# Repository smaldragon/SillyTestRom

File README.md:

# SillyTestRom

"SillyTestRom" is a simple discrete logic mapper for the famicom/clone that I made for my own personal messing around with homebrew, there are currently no plans to use this in anything.

* 512 KiB PRG-FLASH (partially re-writabble for game saves)
* 8KiB CHR-RAM
* Arbitrary Nametable Mirroring!

I mainly see this as an extended AxROM, compared to similar options, the main upsides of this board are low-part count and compatibility with famiclones that don't support 4-screen mirroring.

The board can also be bodged into other configurations. Currently 2 configurations of this board are being considered (by me), A and B.

> **NOTE** Everything here is a WIP and subject to change!

## Hardware

Mapper ICs:
* 74HC377 (8bit register with enable, mapper register)
* 74HC153 (dual 4→1 multiplexer, mirroring logic and chip-enable not gate)
* some diode/resistor logic

## Register (0x8000-0x9FFF)

There are no Bus Conflicts.

Its possible I may switch the PRG Bank control to use A0-3 instead, as code is always aware of which bank its currently running from, this could save code from always having to OR the graphics and bank bits together when only changing graphics values.

### A Wiring

```
Data
MMMM BBBB
|    |
|    +--- PRG Bank (32K@$8000)
+-------- Nametable Mirroring

Potential Address+Data Alternative:

Address | Data
   BBBB | xxxx.MMMM
      |        +-------- Nametable Mirroring
      +----------------- PRG Bank (32K@$8000)
```

Each Mirroring bit controls the nametable (A or B) visible at each of the 4 logical slots, allowing for any type of (non-extended) mirroring, ie:

```
* $Ax -> Vertical
   AB
   AB
* $Cx -> Horizontal
   AA
   BB
* $0x -> Single Screen A
   AA
   AA
* $Fx -> Single Screen B
   BB
   BB
* $6x -> Diagonal
   AB
   BA
 (etc..)
```

## B Wiring

The B version loses the support for horizontal and vertical mirroring, but allows for 4 CHR-RAM banks, this is motivated by the similar cost of 8KiB and 32KiB sram chips.

```
CCMM BBBB
| |  |
| |  +--- PRG Bank (32K@$8000)
| +------ Nametable Mirroring
+-------- CHR Bank (8K@ppu$0000)

Potential Address+Data Alternative:

Address | Data
   BBBB | xxCC.xxMM
      |     |    +------ Nametable Mirroring
      |     +----------- CHR Bank (8K@ppu$0000)
      +----------------- PRG Bank (32K@$8000)
```

In this case the mirroring bits are as follows:

```
(bits)
* 00: AA
      AA

* 01: BA
      AB

* 10: AB
      BA

* 11: BB
      BB
```

## Flash Saves (0xA000-0xFFFF)

This area is available for writing data to the 39sf flash chip. Check the datasheet for info on how this is done.

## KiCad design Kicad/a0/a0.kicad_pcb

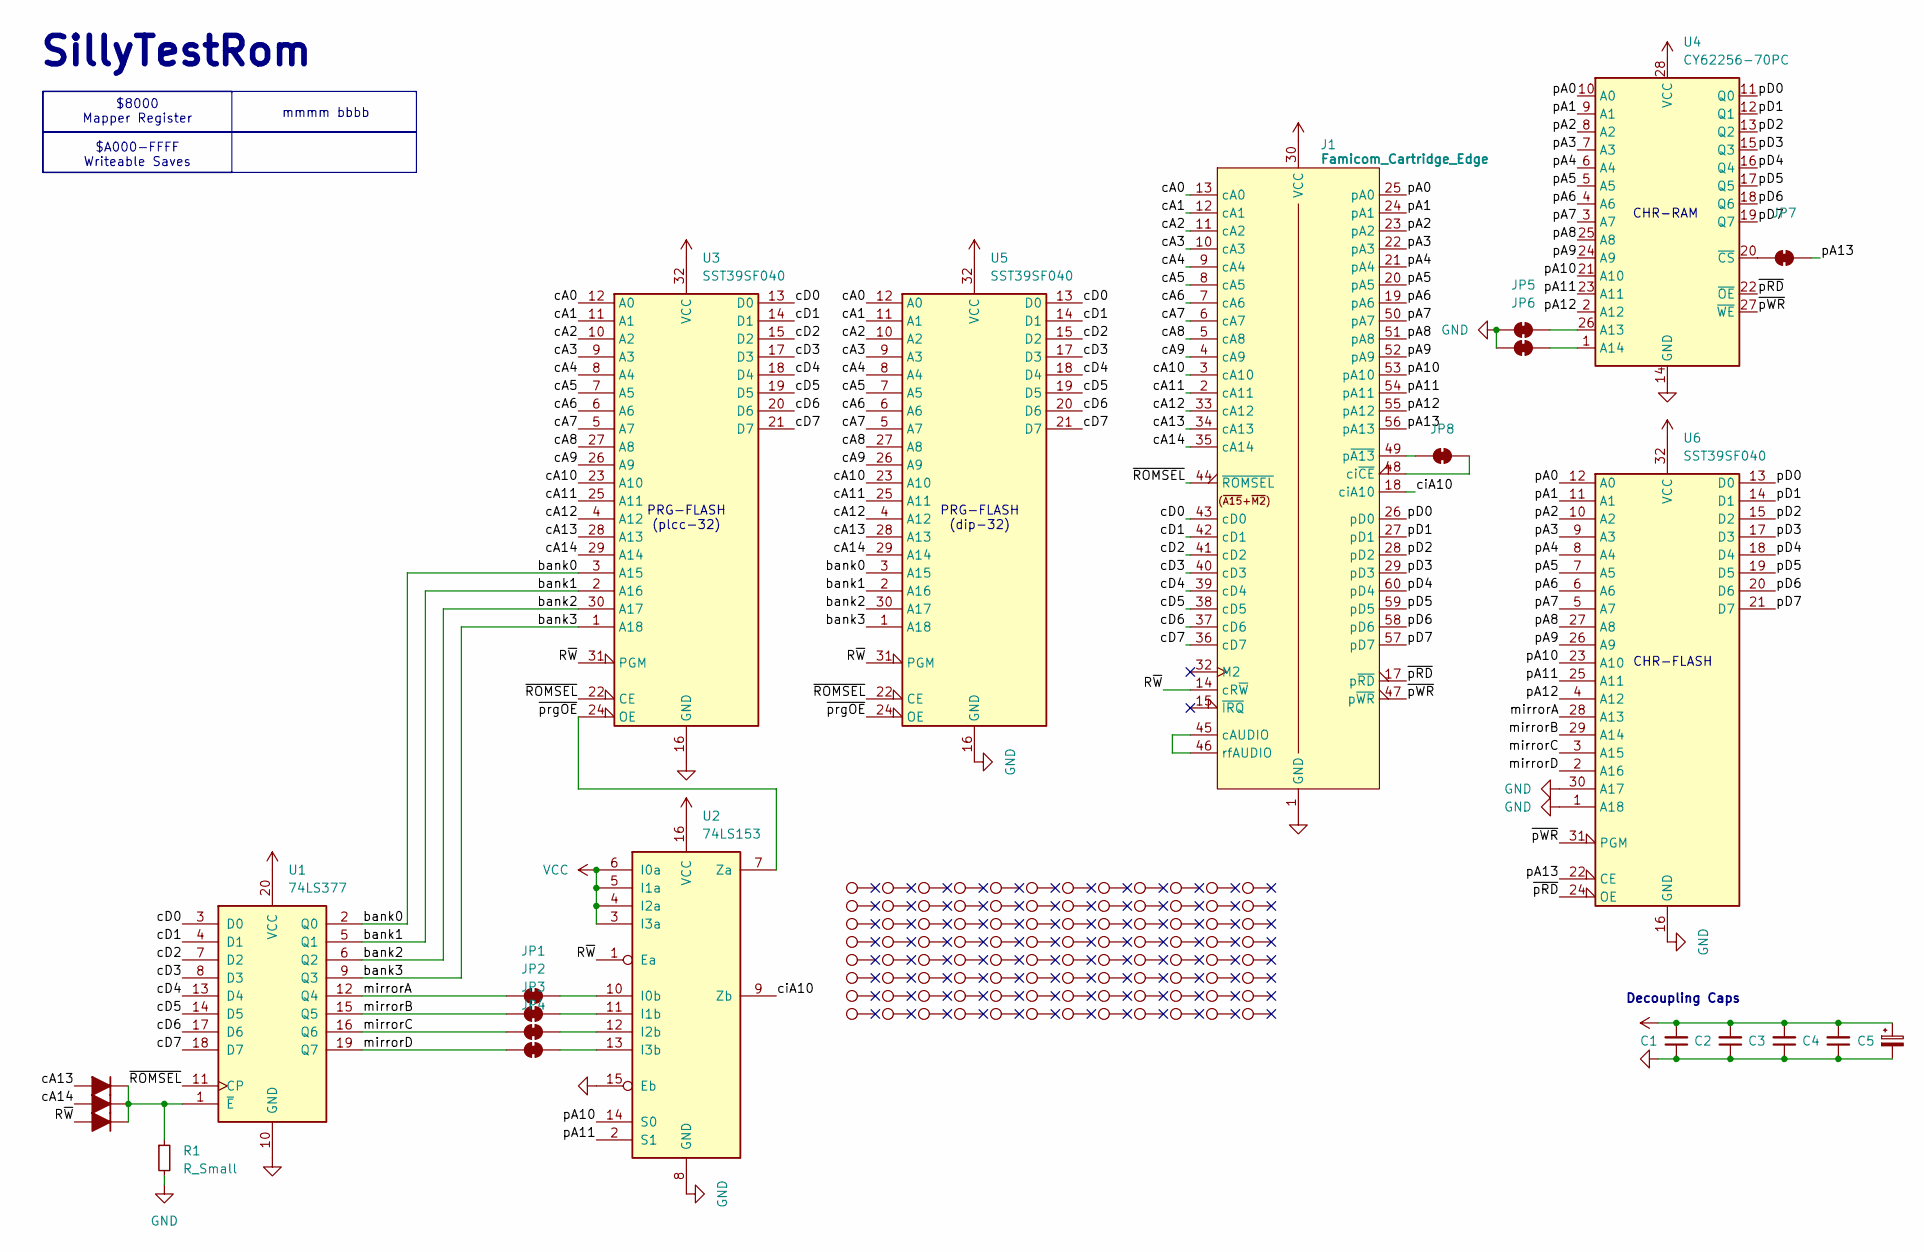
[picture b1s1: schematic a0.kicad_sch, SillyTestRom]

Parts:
C1, C2, C3, C4: C_Small; C_Disc_D3.0mm_W1.6mm_P2.50mm
C5: C_Polarized_Small; CP_Radial_D5.0mm_P2.50mm
D1, D2, D3: 1N4148; D_DO-35_SOD27_P7.62mm_Horizontal
J1: Famicom_Cartridge_Edge; Famicom Cartridge Edge Connector (long legs)
JP1, JP2, JP3, JP4, JP5, JP6, JP7, JP8: SolderJumper_2_Bridged; SolderJumper-2_P1.3mm_Bridged2Bar_RoundedPad1.0x1.5mm
R1: R_Small; R_Axial_DIN0204_L3.6mm_D1.6mm_P7.62mm_Horizontal
TP1, TP2, TP3, TP4, TP5, TP6, TP7, TP8, TP9, TP10, TP11, TP12, TP13, TP14, TP15, TP16, TP17, TP18, TP19, TP20, TP21, TP22, TP23, TP24, TP25, TP26, TP27, TP28, TP29, TP30, TP31, TP32, TP33, TP34, TP35, TP36, TP37, TP38, TP39, TP40, TP41, TP42, TP43, TP44, TP45, TP46, TP47, TP48, TP49, TP50, TP51, TP52, TP53, TP54, TP55, TP56, TP57, TP58, TP59, TP60, TP61, TP62, TP63, TP64, TP65, TP66, TP67, TP68, TP69, TP70, TP71, TP72, TP73, TP74, TP75, TP76, TP77, TP78, TP79, TP80, TP81, TP82, TP83, TP84, TP85, TP86, TP87, TP88, TP89, TP90, TP91, TP92, TP93, TP94, TP95, TP96: TestPoint; TestPoint_THTPad_D1.5mm_Drill1mm
U1: 74LS377; DIP-20_W7.62mm
U2: 74LS153; DIP-16_W7.62mm
U3, U6: SST39SF040; PLCC-32_SMD-Socket
U4: CY62256-70PC; DIP-28_W15.24mm
U5: SST39SF040; DIP-32_W15.24mm

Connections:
/R~W: D2.2 (A), J1.14 (cR~W), U2.1 (Ea), U3.31 (PGM), U5.31 (PGM)
/bank0: U1.2 (Q0), U3.3 (A15), U5.3 (A15)
/bank1: U1.5 (Q1), U3.2 (A16), U5.2 (A16)
/bank2: U1.6 (Q2), U3.30 (A17), U5.30 (A17)
/bank3: U1.9 (Q3), U3.1 (A18), U5.1 (A18)
/cA0: J1.13 (cA0), U3.12 (A0), U5.12 (A0)
/cA1: J1.12 (cA1), U3.11 (A1), U5.11 (A1)
/cA2: J1.11 (cA2), U3.10 (A2), U5.10 (A2)
/cA3: J1.10 (cA3), U3.9 (A3), U5.9 (A3)
/cA4: J1.9 (cA4), U3.8 (A4), U5.8 (A4)
/cA5: J1.8 (cA5), U3.7 (A5), U5.7 (A5)
/cA6: J1.7 (cA6), U3.6 (A6), U5.6 (A6)
/cA7: J1.6 (cA7), U3.5 (A7), U5.5 (A7)
/cA8: J1.5 (cA8), U3.27 (A8), U5.27 (A8)
/cA9: J1.4 (cA9), U3.26 (A9), U5.26 (A9)
/cA10: J1.3 (cA10), U3.23 (A10), U5.23 (A10)
/cA11: J1.2 (cA11), U3.25 (A11), U5.25 (A11)
/cA12: J1.33 (cA12), U3.4 (A12), U5.4 (A12)
/cA13: D3.2 (A), J1.34 (cA13), U3.28 (A13), U5.28 (A13)
/cA14: D1.2 (A), J1.35 (cA14), U3.29 (A14), U5.29 (A14)
/cD0: J1.43 (cD0), U1.3 (D0), U3.13 (D0), U5.13 (D0)
/cD1: J1.42 (cD1), U1.4 (D1), U3.14 (D1), U5.14 (D1)
/cD2: J1.41 (cD2), U1.7 (D2), U3.15 (D2), U5.15 (D2)
/cD3: J1.40 (cD3), U1.8 (D3), U3.17 (D3), U5.17 (D3)
/cD4: J1.39 (cD4), U1.13 (D4), U3.18 (D4), U5.18 (D4)
/cD5: J1.38 (cD5), U1.14 (D5), U3.19 (D5), U5.19 (D5)
/cD6: J1.37 (cD6), U1.17 (D6), U3.20 (D6), U5.20 (D6)
/cD7: J1.36 (cD7), U1.18 (D7), U3.21 (D7), U5.21 (D7)
/ciA10: J1.18 (ciA10), U2.9 (Zb)
/mirrorA: JP1.1 (A), U1.12 (Q4), U6.28 (A13)
/mirrorB: JP2.1 (A), U1.15 (Q5), U6.29 (A14)
/mirrorC: JP3.1 (A), U1.16 (Q6), U6.3 (A15)
/mirrorD: JP4.1 (A), U1.19 (Q7), U6.2 (A16)
/pA0: J1.25 (pA0), U4.10 (A0), U6.12 (A0)
/pA1: J1.24 (pA1), U4.9 (A1), U6.11 (A1)
/pA2: J1.23 (pA2), U4.8 (A2), U6.10 (A2)
/pA3: J1.22 (pA3), U4.7 (A3), U6.9 (A3)
/pA4: J1.21 (pA4), U4.6 (A4), U6.8 (A4)
/pA5: J1.20 (pA5), U4.5 (A5), U6.7 (A5)
/pA6: J1.19 (pA6), U4.4 (A6), U6.6 (A6)
/pA7: J1.50 (pA7), U4.3 (A7), U6.5 (A7)
/pA8: J1.51 (pA8), U4.25 (A8), U6.27 (A8)
/pA9: J1.52 (pA9), U4.24 (A9), U6.26 (A9)
/pA10: J1.53 (pA10), U2.14 (S0), U4.21 (A10), U6.23 (A10)
/pA11: J1.54 (pA11), U2.2 (S1), U4.23 (A11), U6.25 (A11)
/pA12: J1.55 (pA12), U4.2 (A12), U6.4 (A12)
/pA13: J1.56 (pA13), JP7.2 (B), U6.22 (CE)
/pD0: J1.26 (pD0), U4.11 (Q0), U6.13 (D0)
/pD1: J1.27 (pD1), U4.12 (Q1), U6.14 (D1)
/pD2: J1.28 (pD2), U4.13 (Q2), U6.15 (D2)
/pD3: J1.29 (pD3), U4.15 (Q3), U6.17 (D3)
/pD4: J1.60 (pD4), U4.16 (Q4), U6.18 (D4)
/pD5: J1.59 (pD5), U4.17 (Q5), U6.19 (D5)
/pD6: J1.58 (pD6), U4.18 (Q6), U6.20 (D6)
/pD7: J1.57 (pD7), U4.19 (Q7), U6.21 (D7)
/~ROMSEL: J1.44 (~ROMSEL), U1.11 (CP), U3.22 (CE), U5.22 (CE)
/~pRD: J1.17 (p~RD), U4.22 (~OE), U6.24 (OE)
/~pWR: J1.47 (p~WR), U4.27 (~WE), U6.31 (PGM)
/~prgOE: U2.7 (Za), U3.24 (OE), U5.24 (OE)
GND: C1.1, C2.1, C3.1, C4.1, C5.2, J1.1 (GND), J1.16 (GND), JP5.1 (A), JP6.1 (A), R1.2, U1.10 (GND), U2.8 (GND), U2.15 (Eb), U3.16 (GND), U4.14 (GND), U5.16 (GND), U6.1 (A18), U6.16 (GND), U6.30 (A17)
unnamed: D1.1 (K), D2.1 (K), D3.1 (K), R1.1, U1.1 (~E)
unnamed: J1.45 (cAUDIO), J1.46 (rfAUDIO)
unnamed: J1.48 (ci~CE), JP8.1 (A)
unnamed: J1.49 (p~A13), JP8.2 (B)
unnamed: JP1.2 (B), U2.10 (I0b)
unnamed: JP2.2 (B), U2.11 (I1b)
unnamed: JP3.2 (B), U2.12 (I2b)
unnamed: JP4.2 (B), U2.13 (I3b)
unnamed: JP5.2 (B), U4.26 (A13)
unnamed: JP6.2 (B), U4.1 (A14)
unnamed: JP7.1 (A), U4.20 (~CS)
VCC: C1.2, C2.2, C3.2, C4.2, C5.1, J1.30 (VCC), J1.31 (VCC), U1.20 (VCC), U2.3 (I3a), U2.4 (I2a), U2.5 (I1a), U2.6 (I0a), U2.16 (VCC), U3.32 (VCC), U4.28 (VCC), U5.32 (VCC), U6.32 (VCC)

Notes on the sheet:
SillyTestRom
CHR-RAM
mmmm bbbb
PRG-FLASH (dip-32)
CHR-FLASH
PRG-FLASH (plcc-32)
Decoupling Caps
$8000 Mapper Register $A000-FFFF Writeable Saves

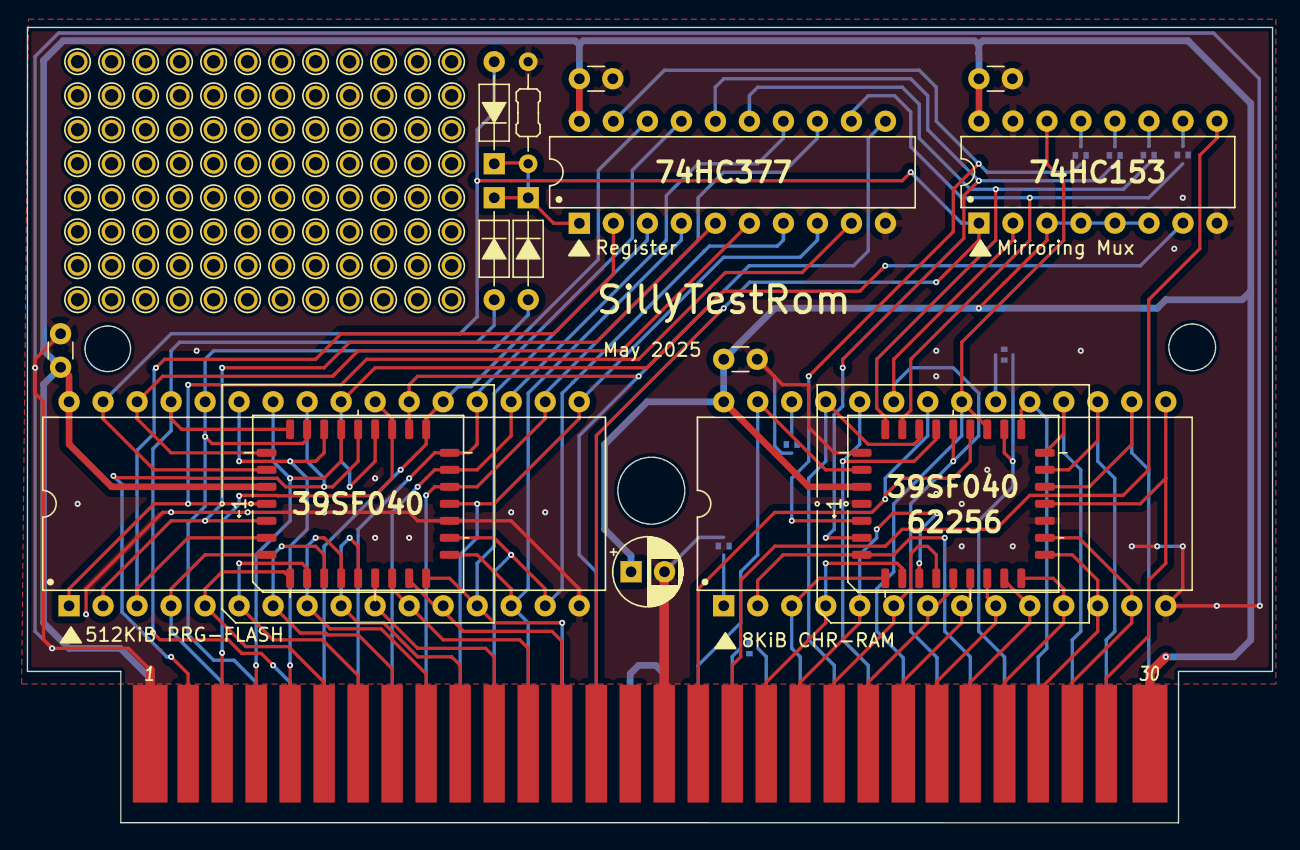
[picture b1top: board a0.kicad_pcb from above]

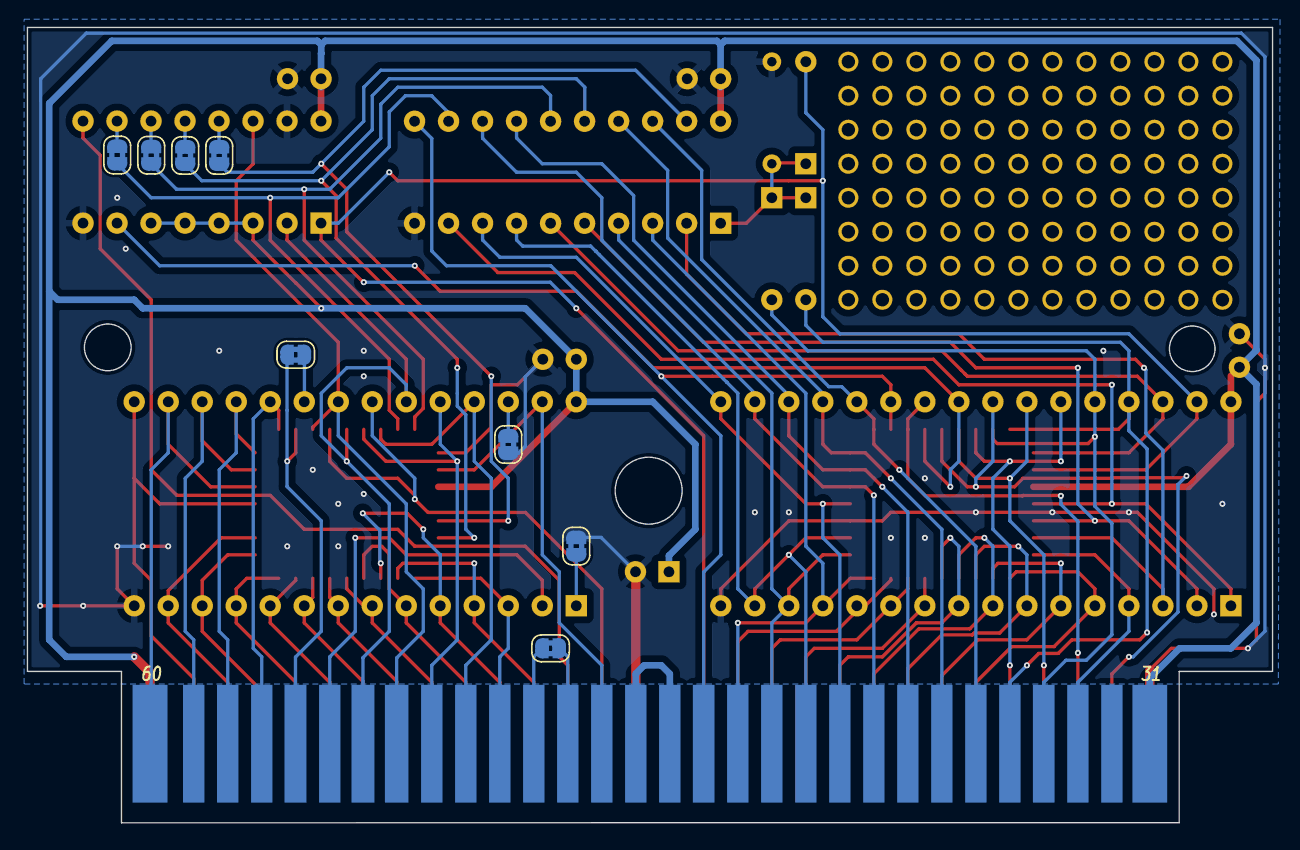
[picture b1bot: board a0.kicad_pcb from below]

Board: 2 copper layers, 93.0 x 59.4 mm, 120 parts (8 on the bottom side), 72 nets.

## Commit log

2025-05-14 Add kicad files
2025-05-16 More README.md info
2025-05-16 fix mistake in README
